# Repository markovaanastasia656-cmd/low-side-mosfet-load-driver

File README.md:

# low-side-mosfet-load-driver
A two-layer KiCad PCB implementing a logic-controlled low-side MOSFET switch for small DC loads using the AO3400A MOSFET.

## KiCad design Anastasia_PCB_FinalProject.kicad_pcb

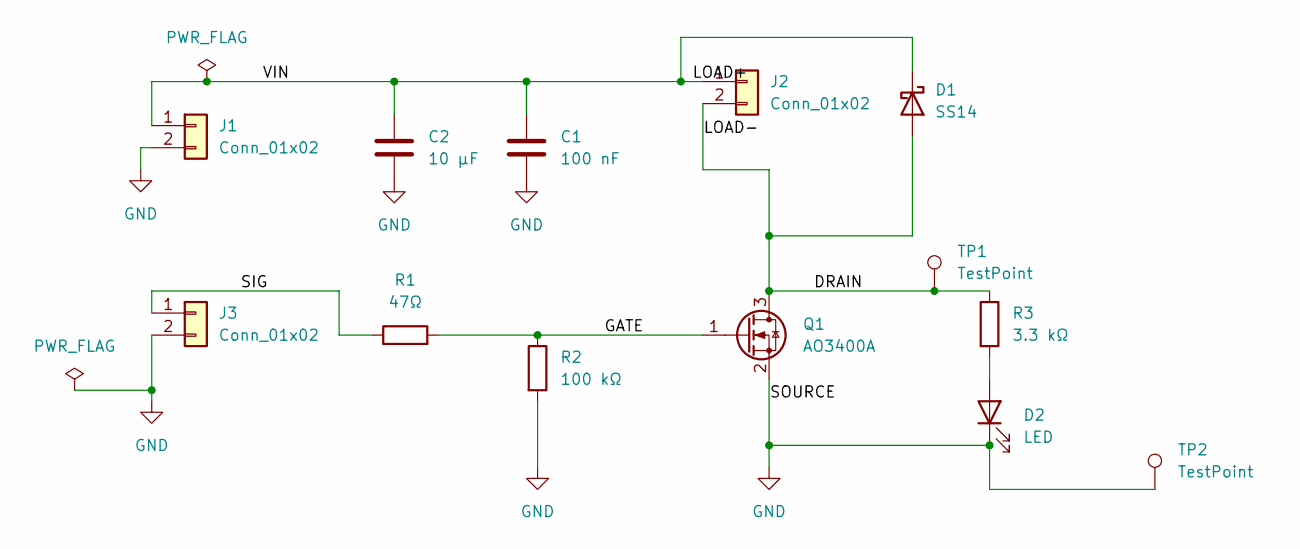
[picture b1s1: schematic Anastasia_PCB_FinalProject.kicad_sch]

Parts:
C1: 100 nF; C_0603_1608Metric
C2: 10 μF; C_0805_2012Metric
D1: SS14; D_SMA
D2: LED; LED_0805_2012Metric
J1, J2, J3: Conn_01x02; PinHeader_1x02_P2.54mm_Vertical
Q1: AO3400A; SOT-23
R1: 47Ω; R_0603_1608Metric
R2: 100 kΩ; R_0603_1608Metric
R3: 3.3 kΩ; R_0603_1608Metric
TP1, TP2: TestPoint; TestPoint_Pad_D1.0mm

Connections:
/DRAIN: D1.2 (A), J2.2, Q1.3 (D), R3.1, TP1.1 (1_1)
/GATE: Q1.1 (G), R1.2, R2.1
/LOAD+: C1.1, C2.1, D1.1 (K), J1.1, J2.1
/SIG: J3.1, R1.1
GND: C1.2, C2.2, D2.1 (K), J1.2, J3.2, Q1.2 (S), R2.2, TP2.1 (1_1)
unnamed: D2.2 (A), R3.2

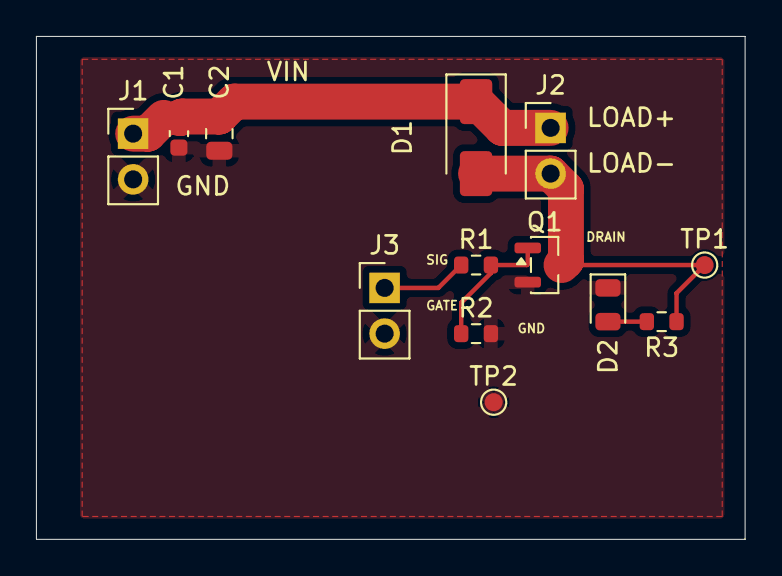
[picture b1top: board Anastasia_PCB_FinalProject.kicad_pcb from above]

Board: 2 copper layers, 39.4 x 27.9 mm, 13 parts (0 on the bottom side), 6 nets.

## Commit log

2026-05-31 Create final examination report for MOSFET driver
    Added comprehensive report for the Low-Side MOSFET Load Driver project, detailing design, verification, and manufacturing outputs.
2026-05-31 Fix formatting of figures in the report
2026-06-02 Rename Low_Side_MOSFET_Load_Driver_Report (2).md to Low_Side_MOSFET_Load_Driver_Report .md
